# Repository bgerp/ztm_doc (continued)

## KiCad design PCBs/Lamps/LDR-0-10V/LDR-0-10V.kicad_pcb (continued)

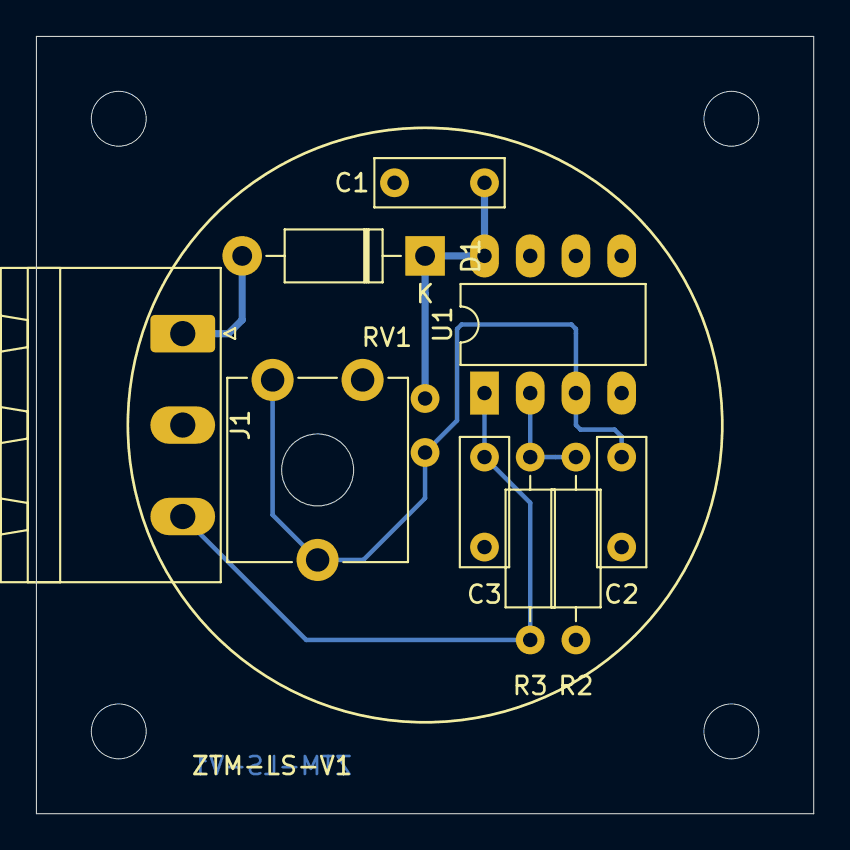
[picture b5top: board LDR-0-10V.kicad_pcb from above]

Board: 2 copper layers, 43.2 x 43.2 mm, 10 parts (1 on the bottom side), 6 nets.

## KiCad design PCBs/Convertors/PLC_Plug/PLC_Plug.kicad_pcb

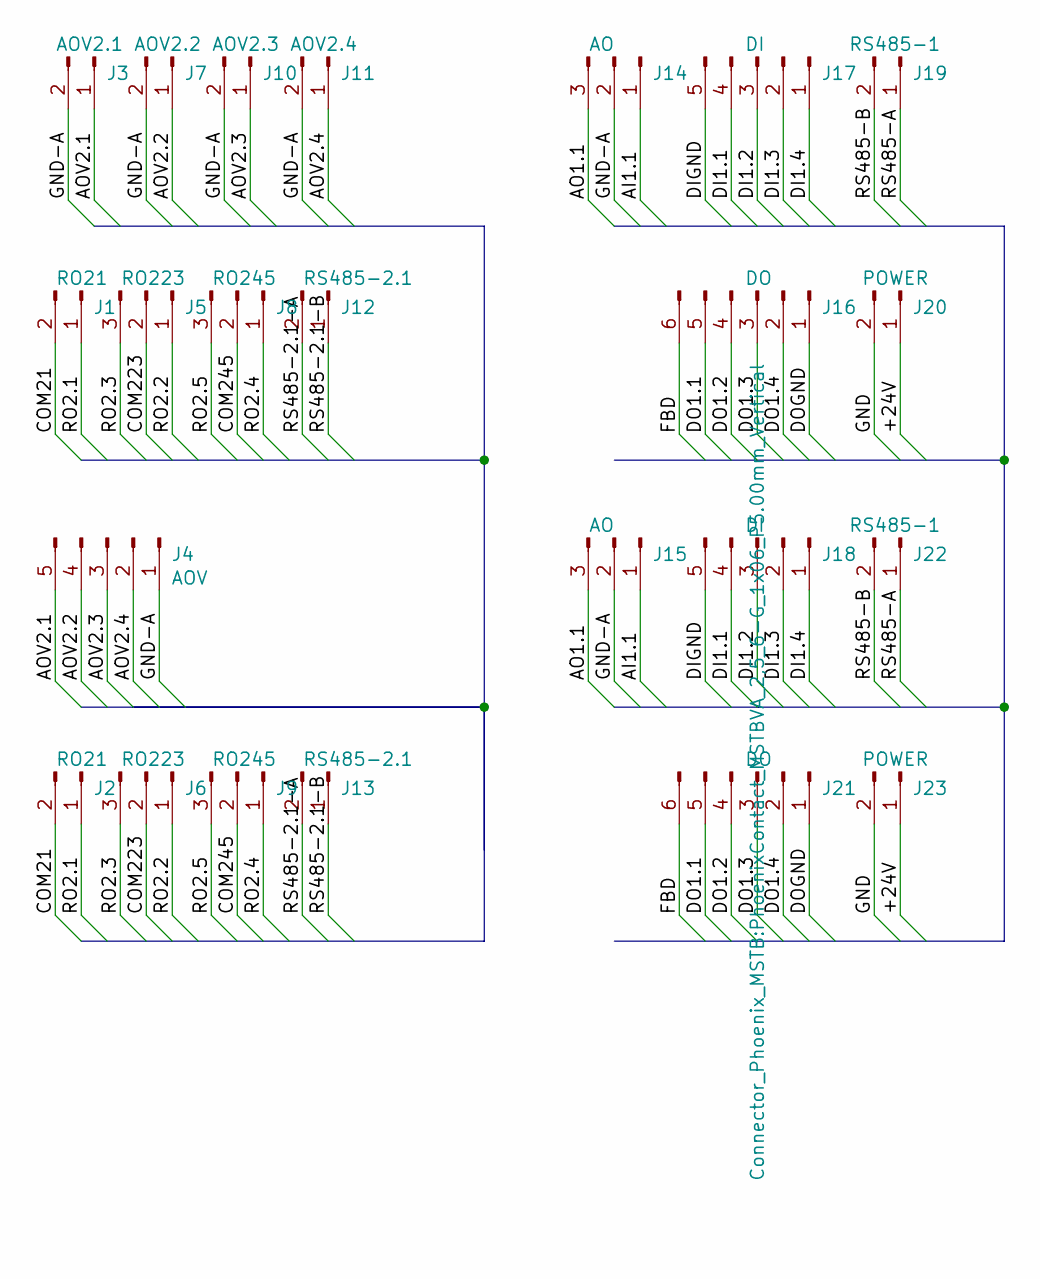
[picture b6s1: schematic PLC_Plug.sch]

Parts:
J1, J2: RO21; PhoenixContact_MSTBVA_2,5_2-G_1x02_P5.00mm_Vertical
J3: AOV2.1; PhoenixContact_MSTBVA_2,5_2-G_1x02_P5.00mm_Vertical
J4: AOV; PhoenixContact_MSTBVA_2,5_5-G_1x05_P5.00mm_Vertical
J5, J6: RO223; PhoenixContact_MSTBVA_2,5_3-G_1x03_P5.00mm_Vertical
J7: AOV2.2; PhoenixContact_MSTBVA_2,5_2-G_1x02_P5.00mm_Vertical
J8, J9: RO245; PhoenixContact_MSTBVA_2,5_3-G_1x03_P5.00mm_Vertical
J10: AOV2.3; PhoenixContact_MSTBVA_2,5_2-G_1x02_P5.00mm_Vertical
J11: AOV2.4; PhoenixContact_MSTBVA_2,5_2-G_1x02_P5.00mm_Vertical
J12, J13: RS485-2.1; PhoenixContact_MSTBVA_2,5_2-G_1x02_P5.00mm_Vertical
J14, J15: AO; PhoenixContact_MSTBVA_2,5_3-G_1x03_P5.00mm_Vertical
J16, J21: DO; PhoenixContact_MSTBVA_2,5_6-G_1x06_P5.00mm_Vertical
J17, J18: DI; PhoenixContact_MSTBVA_2,5_5-G_1x05_P5.00mm_Vertical
J19, J22: RS485-1; PhoenixContact_MSTBVA_2,5_2-G_1x02_P5.00mm_Vertical
J20, J23: POWER; PhoenixContact_MSTBVA_2,5_2-G_1x02_P5.00mm_Vertical

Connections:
/+24V: J20.1, J23.1
/AI1.1: J14.1, J15.1
/AO1.1: J14.3, J15.3
/AOV2.1: J3.1, J4.5
/AOV2.2: J4.4, J7.1
/AOV2.3: J4.3, J10.1
/AOV2.4: J4.2, J11.1
/COM21: J1.2, J2.2
/COM223: J5.2, J6.2
/COM245: J8.2, J9.2
/DI1.1: J17.4, J18.4
/DI1.2: J17.3, J18.3
/DI1.3: J17.2, J18.2
/DI1.4: J17.1, J18.1
/DIGND: J17.5, J18.5
/DO1.1: J16.5, J21.5
/DO1.2: J16.4, J21.4
/DO1.3: J16.3, J21.3
/DO1.4: J16.2, J21.2
/DOGND: J16.1, J21.1
/FBD: J16.6, J21.6
/GND: J20.2, J23.2
/GND-A: J3.2, J4.1, J7.2, J10.2, J11.2, J14.2, J15.2
/RO2.1: J1.1, J2.1
/RO2.2: J5.1, J6.1
/RO2.3: J5.3, J6.3
/RO2.4: J8.1, J9.1
/RO2.5: J8.3, J9.3
/RS485-2.1-A: J12.2, J13.2
/RS485-2.1-B: J12.1, J13.1
/RS485-A: J19.1, J22.1
/RS485-B: J19.2, J22.2

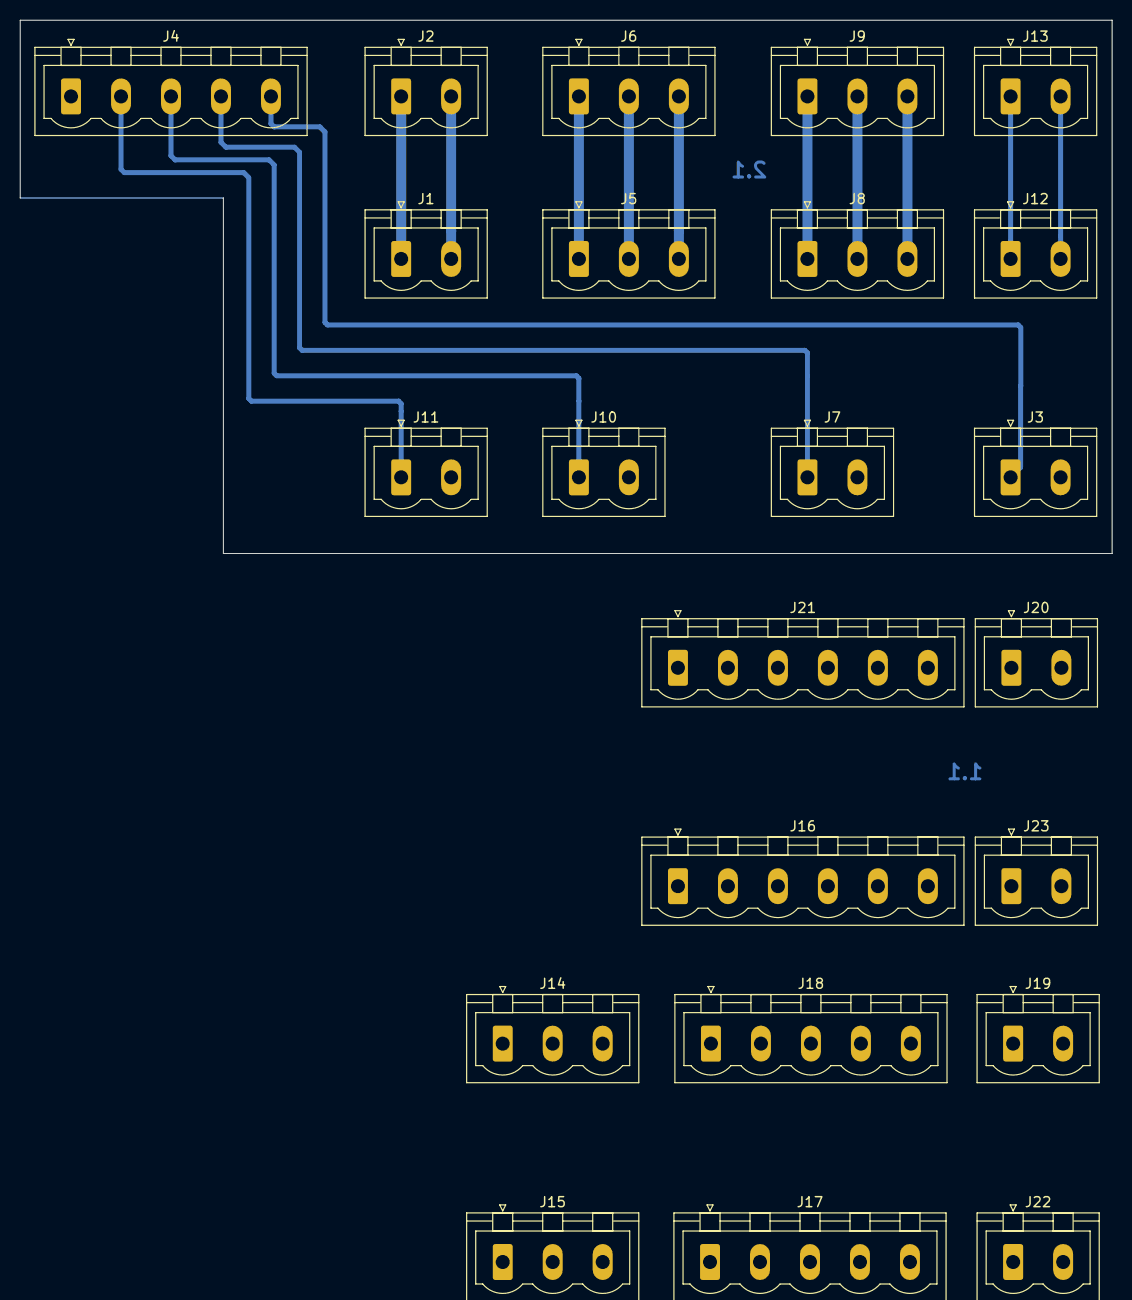
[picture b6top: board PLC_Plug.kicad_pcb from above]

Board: 2 copper layers, 109.2 x 53.3 mm, 23 parts (0 on the bottom side), 32 nets.

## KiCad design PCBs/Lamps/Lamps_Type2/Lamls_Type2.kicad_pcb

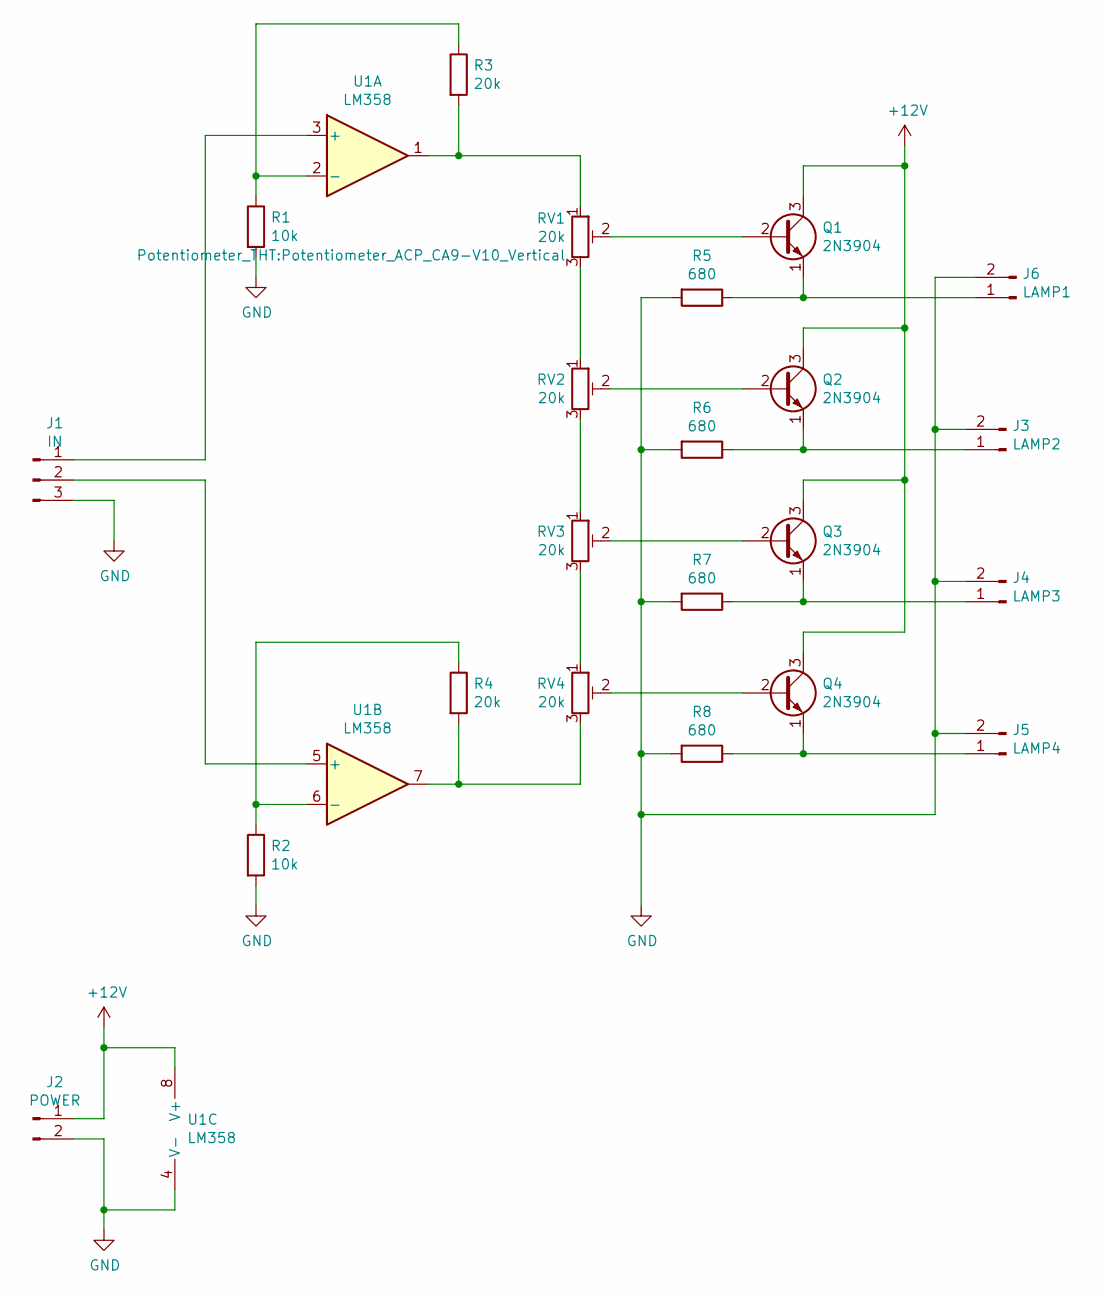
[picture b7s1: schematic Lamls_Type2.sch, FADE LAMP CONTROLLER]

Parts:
J1: IN; TerminalBlock_Phoenix_MKDS-1,5-3_1x03_P5.00mm_Horizontal
J2: POWER; TerminalBlock_Phoenix_MKDS-1,5-2_1x02_P5.00mm_Horizontal
J3: LAMP2; TerminalBlock_Phoenix_MKDS-1,5-2_1x02_P5.00mm_Horizontal
J4: LAMP3; TerminalBlock_Phoenix_MKDS-1,5-2_1x02_P5.00mm_Horizontal
J5: LAMP4; TerminalBlock_Phoenix_MKDS-1,5-2_1x02_P5.00mm_Horizontal
J6: LAMP1; TerminalBlock_Phoenix_MKDS-1,5-2_1x02_P5.00mm_Horizontal
Q1, Q2, Q3, Q4: 2N3904; TO-92_Inline_Wide
R1, R2: 10k; R_Axial_DIN0207_L6.3mm_D2.5mm_P10.16mm_Horizontal
R3, R4: 20k; R_Axial_DIN0207_L6.3mm_D2.5mm_P10.16mm_Horizontal
R5, R6, R7, R8: 680; R_Axial_DIN0207_L6.3mm_D2.5mm_P10.16mm_Horizontal
RV1, RV2, RV3, RV4: 20k; Potentiometer_ACP_CA9-V10_Vertical
U1: LM358; DIP-8_W7.62mm_LongPads

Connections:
+12V: J2.1, Q1.3 (C), Q2.3 (C), Q3.3 (C), Q4.3 (C), U1.8 (V+)
GND: J1.3, J2.2, J3.2, J4.2, J5.2, J6.2, R1.2, R2.2, R5.2, R6.2, R7.2, R8.2, U1.4 (V-)
unnamed: J1.1, U1.3 (+)
unnamed: J1.2, U1.5 (+)
unnamed: J3.1, Q2.1 (E), R6.1
unnamed: J4.1, Q3.1 (E), R7.1
unnamed: J5.1, Q4.1 (E), R8.1
unnamed: J6.1, Q1.1 (E), R5.1
unnamed: Q1.2 (B), RV1.2
unnamed: Q2.2 (B), RV2.2
unnamed: Q3.2 (B), RV3.2
unnamed: Q4.2 (B), RV4.2
unnamed: R1.1, R3.1, U1.2 (-)
unnamed: R2.1, R4.1, U1.6 (-)
unnamed: R3.2, RV1.1, U1.1
unnamed: R4.2, RV4.3, U1.7
unnamed: RV1.3, RV2.1
unnamed: RV2.3, RV3.1
unnamed: RV3.3, RV4.1

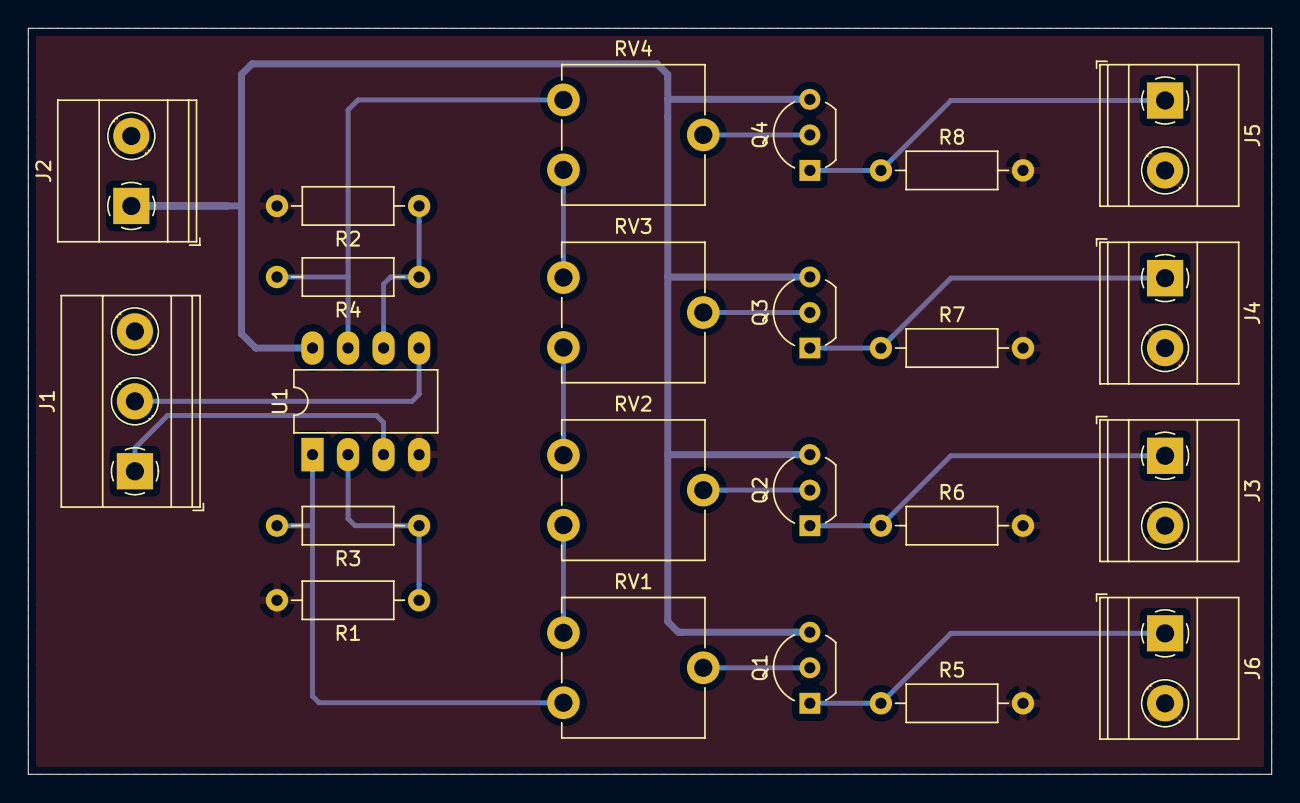
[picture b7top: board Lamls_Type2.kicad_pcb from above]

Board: 2 copper layers, 88.9 x 53.3 mm, 23 parts (0 on the bottom side), 19 nets.

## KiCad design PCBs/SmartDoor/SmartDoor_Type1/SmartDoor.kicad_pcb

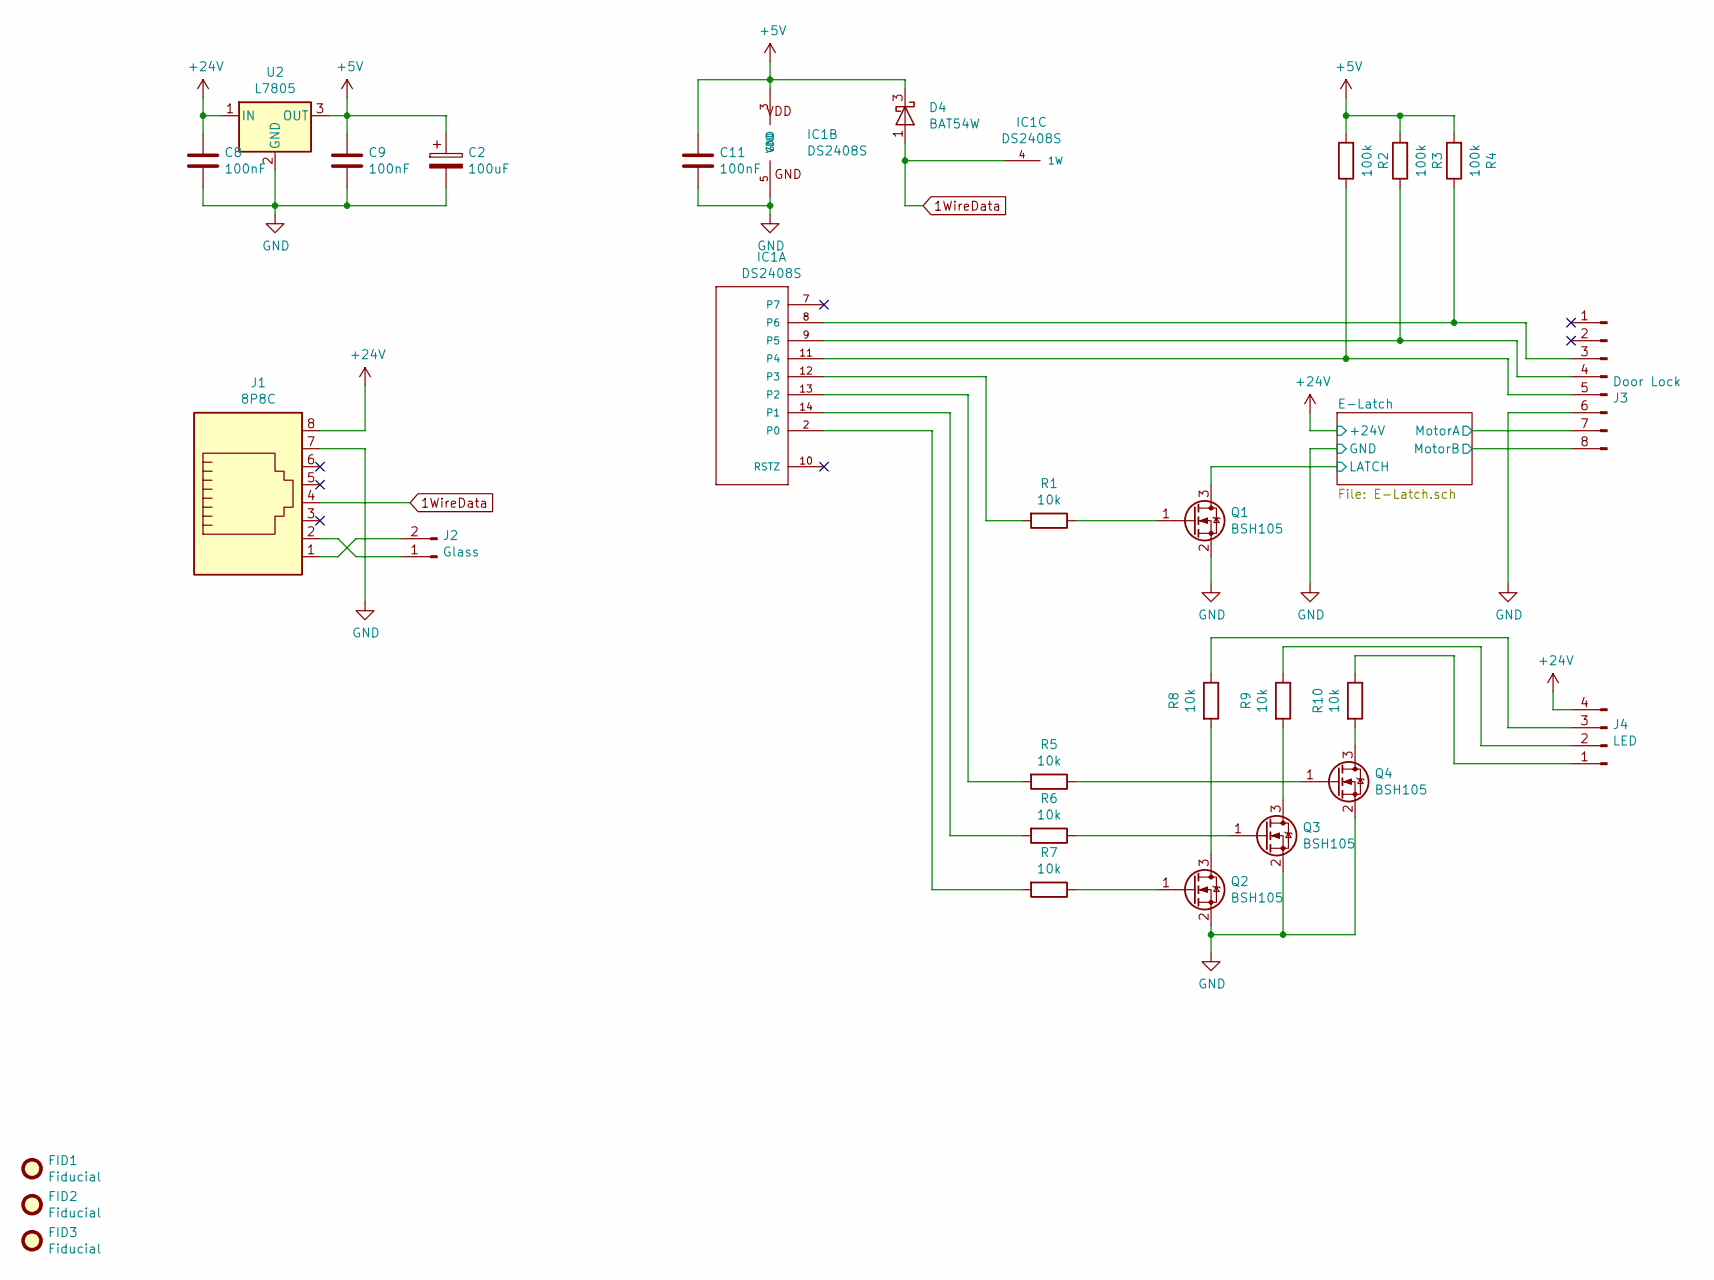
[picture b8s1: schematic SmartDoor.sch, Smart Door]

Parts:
C2: 100uF; CP_Elec_4x5.4
C8, C9, C11: 100nF; C_0805_2012Metric
D4: BAT54W; SOT-323_SC-70
FID1, FID2, FID3: Fiducial; Fiducial_0.75mm_Mask1.5mm
IC1: DS2408S; SOIC-16_3.9x9.9mm_P1.27mm
J1: 8P8C; RJ45_Amphenol_54602-x08_Horizontal
J2: Glass; PhoenixContact_MSTBA_2,5_2-G-5,08_1x02_P5.08mm_Horizontal
J3: Door Lock; PinHeader_1x08_P2.54mm_Horizontal
J4: LED; PhoenixContact_MSTBA_2,5_4-G-5,08_1x04_P5.08mm_Horizontal
Q1, Q2, Q3, Q4: BSH105; SOT-23
R1, R5, R6, R7, R8, R9, R10: 10k; R_0805_2012Metric
R2, R3, R4: 100k; R_0805_2012Metric
U2: L7805; TO-252-3_TabPin2

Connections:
1WireData: D4.1 (A), IC1.4 (1W), J1.4
+5V: C2.1, C9.1, C11.1, D4.3 (K), IC1.3 (VDD), R2.2, R3.2, R4.2, U2.3 (OUT); also elsewhere on the board
+24V: C8.1, J1.8, J4.4, U2.1 (IN); also elsewhere on the board
/E-Latch/LATCH: Q1.3 (D); also elsewhere on the board
/E-Latch/MotorA: J3.7; also elsewhere on the board
/E-Latch/MotorB: J3.8; also elsewhere on the board
GND: C2.2, C8.2, C9.2, C11.2, IC1.5 (GND), J1.7, J3.6, Q1.2 (S), Q2.2 (S), Q3.2 (S), Q4.2 (S), U2.2 (GND); also elsewhere on the board
unnamed: IC1.2 (P0), R7.2
unnamed: IC1.8 (P6), J3.3, R4.1
unnamed: IC1.9 (P5), J3.4, R3.1
unnamed: IC1.11 (P4), J3.5, R2.1
unnamed: IC1.12 (P3), R1.2
unnamed: IC1.13 (P2), R5.2
unnamed: IC1.14 (P1), R6.2
unnamed: J1.1, J2.2
unnamed: J1.2, J2.1
unnamed: J4.1, R10.1
unnamed: J4.2, R9.1
unnamed: J4.3, R8.1
unnamed: Q1.1 (G), R1.1
unnamed: Q2.1 (G), R7.1
unnamed: Q2.3 (D), R8.2
unnamed: Q3.1 (G), R6.1
unnamed: Q3.3 (D), R9.2
unnamed: Q4.1 (G), R5.1
unnamed: Q4.3 (D), R10.2

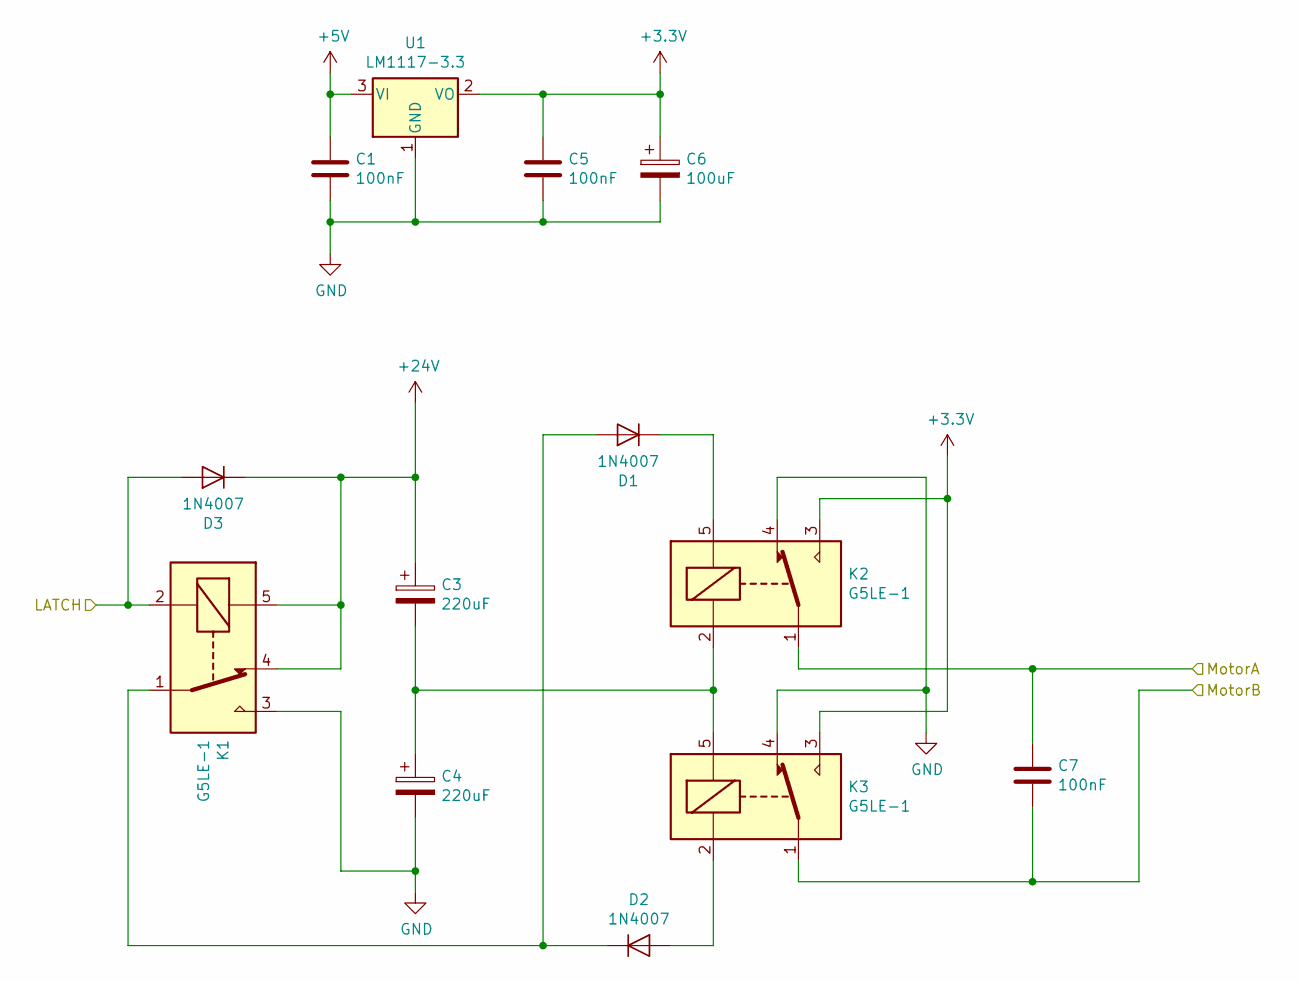
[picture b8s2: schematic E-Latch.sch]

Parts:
C1, C5, C7: 100nF; C_0805_2012Metric
C3, C4: 220uF; CP_Elec_5x5.4
C6: 100uF; CP_Elec_4x4.5
D1, D2, D3: 1N4007; D_SMA
K1, K2, K3: G5LE-1; Relay_SPDT_Omron-G5LE-1
U1: LM1117-3.3; SOT-89-3_Handsoldering

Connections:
+3V3: C5.1, C6.1, K2.3, K3.3, U1.2 (VO)
+5V: C1.1, U1.3 (VI); also elsewhere on the board
+24V: C3.1, D3.1 (K), K1.4, K1.5; also elsewhere on the board
/E-Latch/LATCH: D3.2 (A), K1.2; also elsewhere on the board
/E-Latch/MotorA: C7.1, K2.1; also elsewhere on the board
/E-Latch/MotorB: C7.2, K3.1; also elsewhere on the board
GND: C1.2, C4.2, C5.2, C6.2, K1.3, K2.4, K3.4, U1.1 (GND); also elsewhere on the board
unnamed: C3.2, C4.1, K2.2, K3.5
unnamed: D1.1 (K), K2.5
unnamed: D1.2 (A), D2.1 (K), K1.1
unnamed: D2.2 (A), K3.2

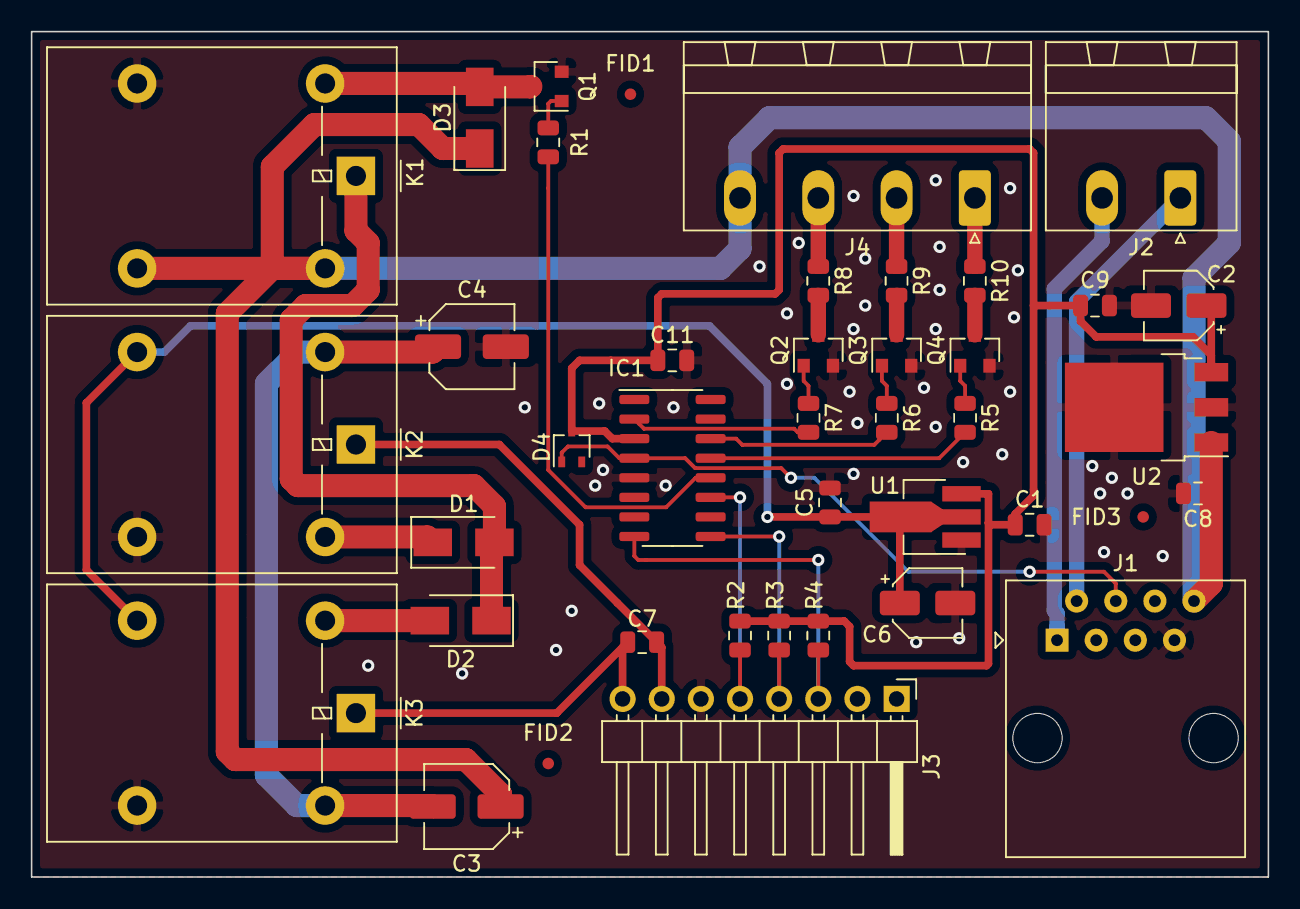
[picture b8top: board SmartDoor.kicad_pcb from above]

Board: 2 copper layers, 80.3 x 54.9 mm, 41 parts (0 on the bottom side), 31 nets.

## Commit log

2020-11-05 Add README
2020-11-05 Add ignore files
2020-11-05 Add Licenses
2020-11-05 Add READMEs
2020-11-05 Add OfficeCabinet_Type1_L1_3P
2020-11-05 Add OfficeCabinet_Type4_L1_1P
2020-11-05 Add Update export license
2020-11-05 Update git ignore files
2020-11-05 Add Blinds_Type1
2020-11-05 Add Blinds_Type2
2020-11-05 Add Blinds_Type3
2020-11-05 Add PWM_TO_0-10V
2020-11-05 Add E-Latch_Type2
2020-11-05 Add Lamps_Type1
2020-11-05 Add SCH
2020-11-05 Add SmartDoor_Type1
2020-11-05 Fix2
2020-11-05 Update foil 2 of OfficeCabinet_Type1_L1_3P
2020-11-05 Fix export path
2020-11-05 Fix 2 export path
2020-11-05 Fix 3
2020-11-05 Fix 4
2020-11-05 Fix 5
2020-11-05 Fix 6
2020-11-05 Fix 7
2020-11-05 Fix 8
2020-11-05 Fix 9
2020-11-05 Fix 10
2020-11-05 Fix 11
2020-11-06 Fix 12
2020-11-10 Add table of adoption, between devices and cabinet
2020-11-10 Add link to the wiring table
2020-11-18 Update file name and place
2020-11-18 Update wiring link
2020-11-18 Update elements of schematic
2021-03-01 Add tablet documentation
2021-03-02 Version 3 for door latch controller inhouse mounting
2021-03-04 Update device
2021-04-01 Add signal for the out door
2021-04-01 Update README file
2021-04-01 Update PDF
2021-04-01 Update project file
2021-04-01 Fix view operation voltage 12
2021-04-01 Add door controller board int the Mounting diagram
2021-04-09 Update schamatics and monting diagrams
2021-04-14 Add schematic and PCB for the test board
2021-04-14 Small changes
2021-04-19 Add schematic PDF for lamps controller
2021-04-30 Add 0-10V experimantal board for light intensity detection
2021-05-05 Add PDF export for the e-schema
2021-05-12 Add BOM (CSV/XML)
2021-05-12 Add 2D/3D exports
2021-05-12 Update PDF schematic
2021-05-12 Add components values. Add PCB. Update project.
2021-05-12 Change file extention
2021-05-12 Add schematic and nasting on PCB
2021-05-19 General modification beacuse of dome light inflector
2021-05-20 Correction in WRL export
2021-05-25 3D model of the LDR33 light sensor
2021-08-17 Rebuild Type 3 of E-Latch
2021-08-17 Update 3P sch
2021-08-17 Update PLC adapter
2021-08-17 Add 6CH fead efect light controller (SMD)
2021-08-17 Add fiducials for machine ready work
2021-08-17 Add bck files and exports
2021-08-17 Add blinds controler type 4 with analog feedback
2021-08-17 Export fabrication information
2021-10-18 Initial ECHP wiering diagram
2021-10-18 Update LDR-0-10V
2021-11-17 Update ts when open file, use as a source for other folies
2021-11-17 Add mounting prototype for ECHP production
2021-11-17 Update ts when open file
2021-11-17 Add prototypes for office cell, laboratory and smart panel
2021-11-29 Add license to the prototype license
2021-11-29 Add project
2021-11-29 Add exports
2021-11-29 Add reademe file
2021-12-03 Change electrical schematic of offices and labs
2021-12-13 Check
2021-12-13 Check 2
2021-12-13 Check 3
2021-12-13 Check 4
2021-12-13 Check 5
2021-12-17 PXE boot README
2022-09-23 Link devices
2022-11-04 Update ECD concept
2022-11-04 Update ECHP concept
2022-11-04 Add Boilers 1500L
2022-11-04 Add Buffers 3000L
2022-11-07 Update 3P versions
2022-11-08 Add export for 1500l bunkers
2022-11-08 Add export for 3000l bunkers
2022-11-08 Add export for ECD
2022-11-08 Reorganize the 3P offices
2022-11-08 Add export for GRT
2022-11-08 Add export for thermal groups
2022-11-14 Update file tree
2023-02-22 Add Updates for all cabinets
2023-06-13 Add First Flat schematic
2023-06-13 Add noth server room automation cabinet
2023-06-13 Add south server room automation cabinet
2023-11-03 Add fire vent proto schematic
2023-11-03 Add 6.5 cabinet
2023-11-03 Add Convectors Reception cabinet
2023-11-03 Add FLowx resource
2023-11-03 Add 805 office
2023-11-03 Update office v2 single pole L!
2023-11-03 Add flore heating cntroll
2024-11-21 Add example document
2024-11-21 Add QR code
2024-11-21 Update QR code
2024-12-11 Update B1500
2024-12-11 Update B3000
2024-12-11 Update SixPointFive
2024-12-11 Update ECHP
2024-12-11 Add LAMPS data
2024-12-11 Remove old invalid data
2025-01-03 Add fire vent
2025-01-03 Add meteo
2025-01-03 Add pool heating
2025-01-03 Add reception
2025-01-03 Add thermo controllers floor east west
2025-07-28 Update PoolHeating
2025-07-28 Update chanign rooms
